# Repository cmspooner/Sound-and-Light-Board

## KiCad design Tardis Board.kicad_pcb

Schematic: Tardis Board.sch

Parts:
AMP1, AMP2: AmpilfierBoard; Amplifier
Ard1: Arduino_Pro_Micro; ArduinoProMicro
D1: LED; LED_CONNECTOR
D2: 1N5817; D_DO-41_SOD81_P10.16mm_Horizontal
J1: Conn_01x03_Female; LED_CONNECTOR
LS1, LS2: Speaker; LED_CONNECTOR
NP1: NeoPixel_Jewel7; NeoPixel_CONNECTOR
Q1: IRLB8721PBF; TO-220-3_Vertical
SFX1: Adafruit_Audio_FX_SoundBoard; AdafruitAudioFXSoundBoard
SW1: SW_DIP_x01; LED_CONNECTOR
SW2, SW3, SW4, SW5, SW6, SW7: SW_SPDT; LED_CONNECTOR

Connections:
/5v: Ard1.21, NP1.4, SFX1.22, SW2.1 (A), SW3.1 (A), SW4.1 (A), SW5.1 (A), SW6.1 (A), SW7.1 (A)
/SW14: Ard1.15, SW2.2 (B)
/SW15: Ard1.16, SW3.2 (B)
/SW18: Ard1.17, SW4.2 (B)
/SW19: Ard1.18, SW5.2 (B)
/SW20: Ard1.19, SW6.2 (B)
/SW21: Ard1.20, SW7.2 (B)
GND: AMP1.3, AMP1.4, AMP1.6, AMP2.3, AMP2.4, AMP2.6, Ard1.23, J1.2, J1.3, LS1.2, LS2.2, NP1.3, Q1.3 (S), SFX1.12, SFX1.15, SFX1.21, SW2.3 (C), SW3.3 (C), SW4.3 (C), SW5.3 (C), SW6.3 (C), SW7.3 (C)
unnamed: AMP1.2, SFX1.14
unnamed: AMP1.5, LS1.1
unnamed: AMP2.2, SFX1.13
unnamed: AMP2.5, LS2.1
unnamed: Ard1.5, SFX1.9
unnamed: Ard1.6, SFX1.8
unnamed: Ard1.7, SFX1.7
unnamed: Ard1.8, SFX1.6
unnamed: Ard1.9, SFX1.5
unnamed: Ard1.10, SFX1.4
unnamed: Ard1.11, SFX1.3
unnamed: Ard1.12, SFX1.2
unnamed: Ard1.13, Q1.1 (G)
unnamed: Ard1.14, NP1.5
unnamed: D1.1 (K), Q1.2 (D)
unnamed: D2.1 (K), SW1.2
unnamed: D2.2 (A), J1.1
VCC: AMP1.1, AMP2.1, Ard1.24, D1.2 (A), SW1.1

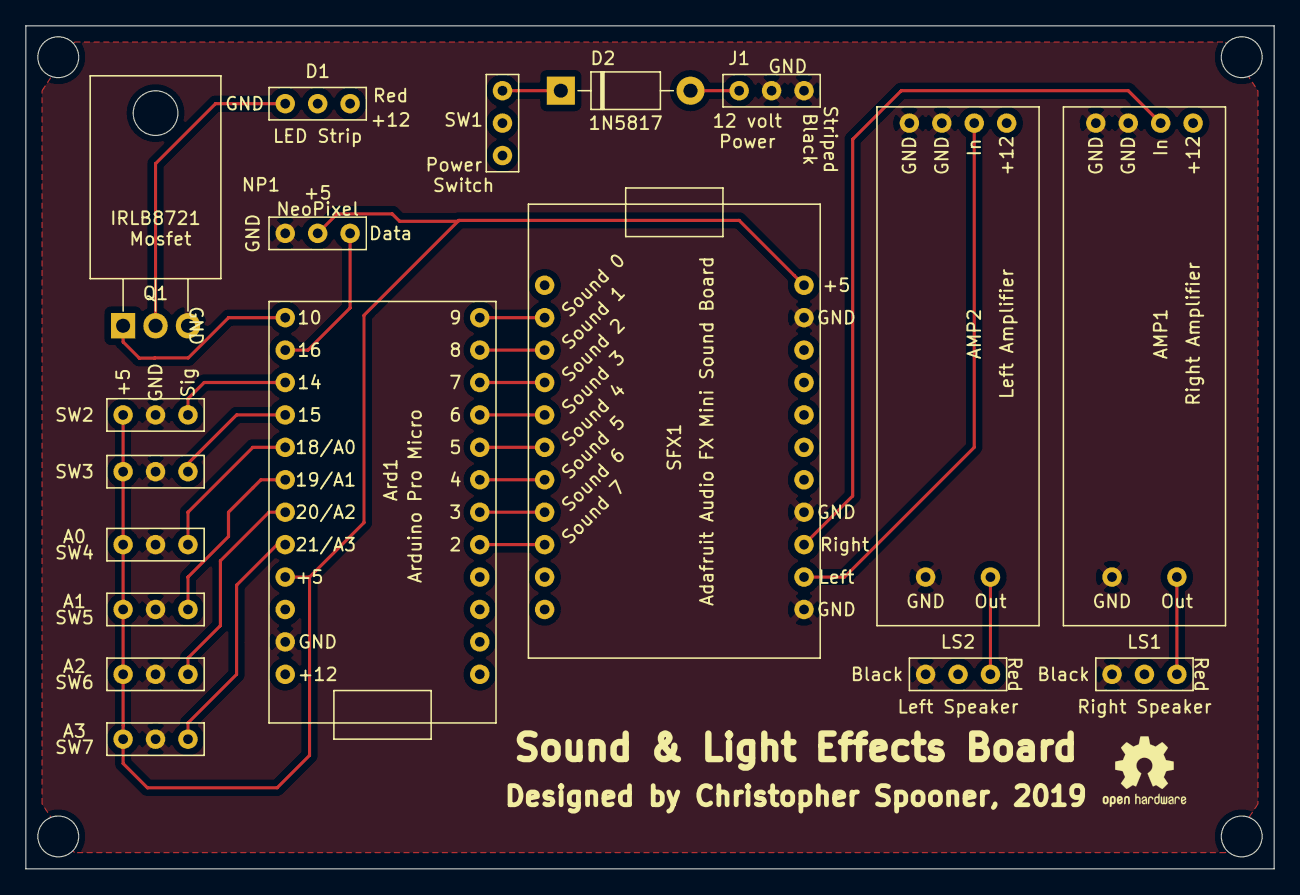
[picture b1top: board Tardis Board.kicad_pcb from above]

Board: 2 copper layers, 97.8 x 66.0 mm, 18 parts (0 on the bottom side), 26 nets.

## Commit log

2019-05-22 set up
2019-05-22 Added Sites for parts
2019-05-24 Version 2 Ordered
2019-05-24 Moved kicad art and made 3d model of 3 pin header
2019-05-28 Changed power label and changed fade rate.
2019-05-31 small updates
